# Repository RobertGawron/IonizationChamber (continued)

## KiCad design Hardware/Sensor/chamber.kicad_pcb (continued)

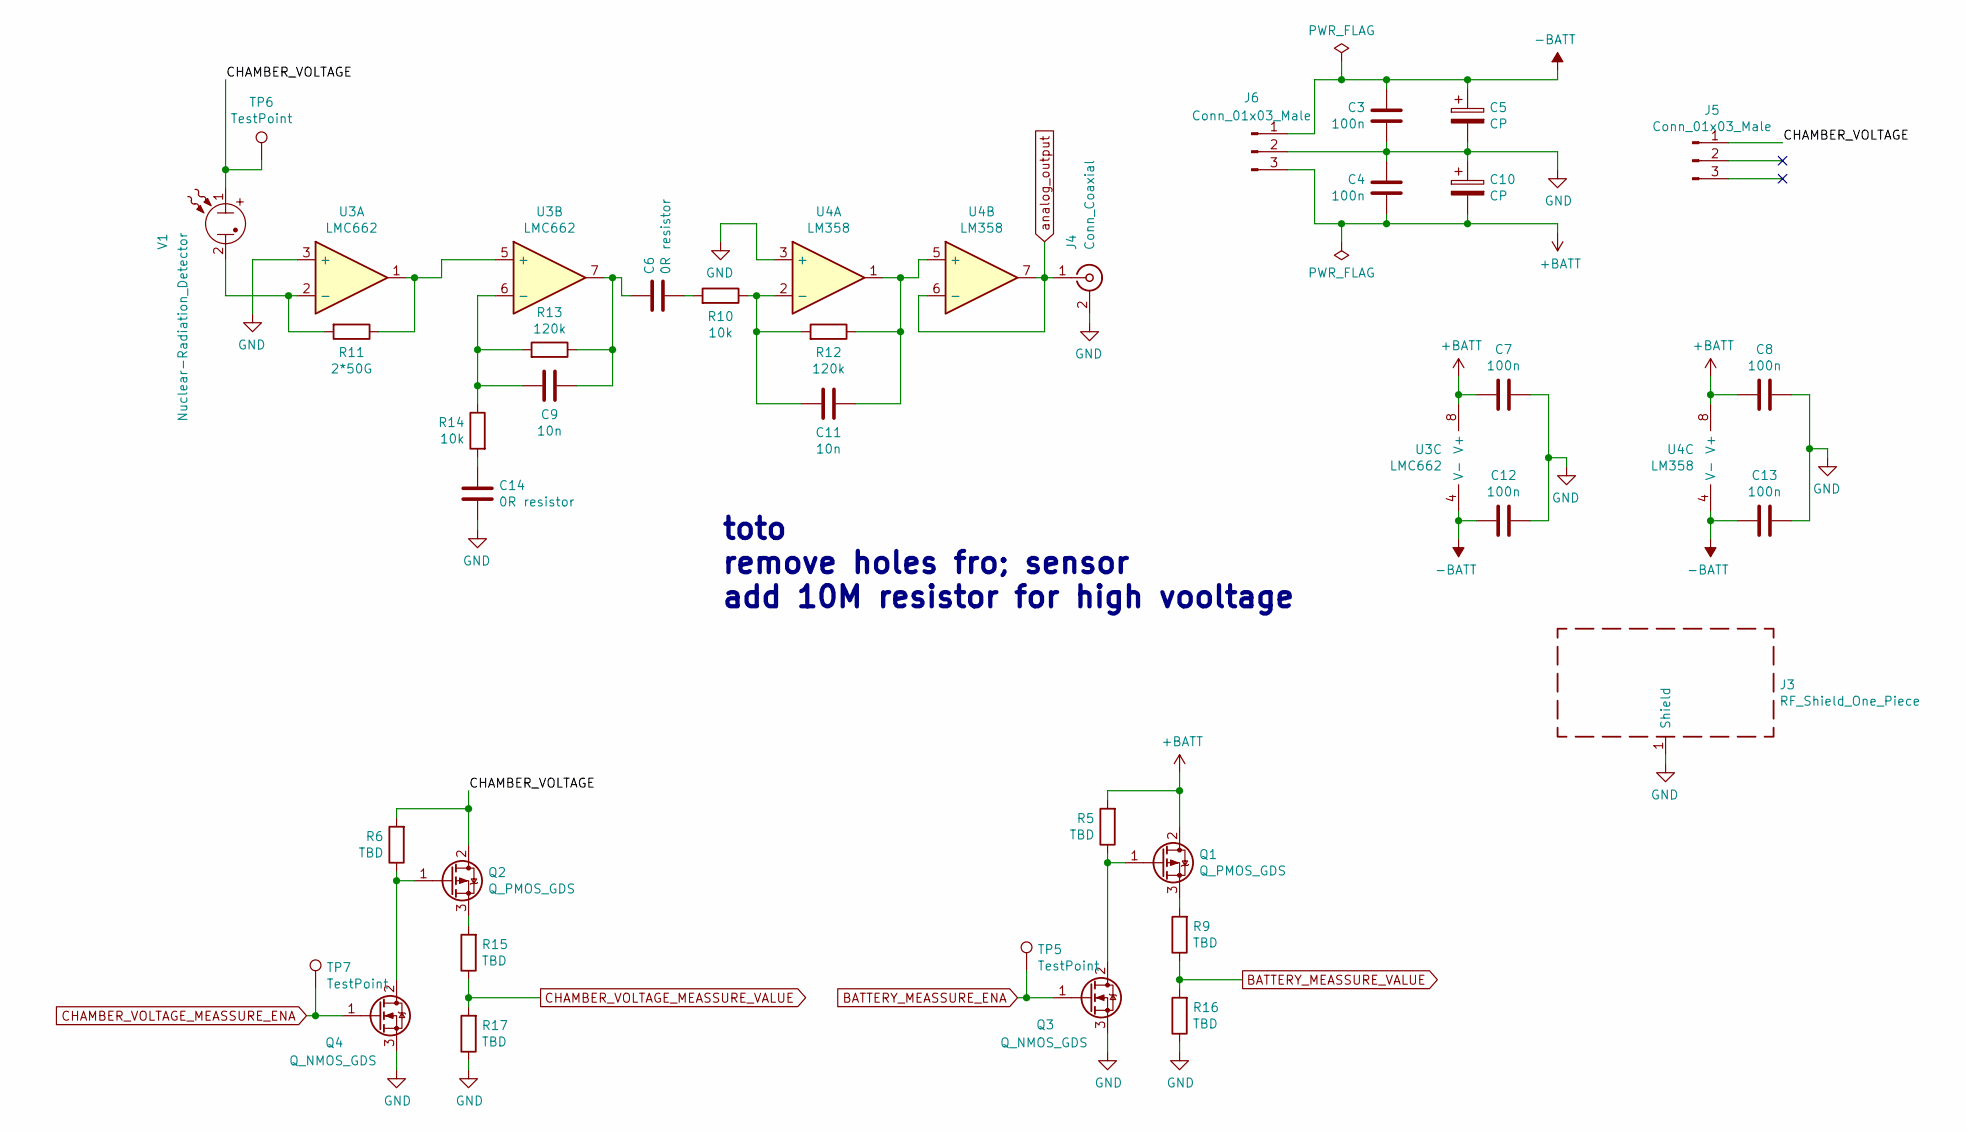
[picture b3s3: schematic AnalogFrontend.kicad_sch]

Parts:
C3, C4, C7, C8, C12, C13: 100n; C_0805_2012Metric; LCSC C282732
C5, C10: CP; CP_Elec_6.3x5.8
C6, C14: 0R resistor; C_0805_2012Metric
C9, C11: 10n; C_0805_2012Metric; LCSC C1710
J3: RF_Shield_One_Piece; RFShield
J4: Conn_Coaxial; SMA_Molex_73251-2200_Horizontal
J5, J6: Conn_01x03_Male; PinSocket_1x03_P2.54mm_Vertical
Q1, Q2: Q_PMOS_GDS; SOT-23
Q3, Q4: Q_NMOS_GDS; SOT-23
R5, R6, R9, R15, R16, R17: TBD; R_0805_2012Metric
R10, R14: 10k; R_0805_2012Metric; LCSC C25744
R11: 2*50G; R_0805_2012Metric
R12, R13: 120k; R_0805_2012Metric; LCSC C17436
TP5, TP7: TestPoint; TestPoint_Pad_D2.0mm
TP6: TestPoint; TestPoint_Loop_D2.60mm_Drill0.9mm_Beaded
U3: LMC662; DIP-8_W7.62mm
U4: LM358; SOIC-8_3.9x4.9mm_P1.27mm; LCSC C7950
V1: Nuclear-Radiation_Detector; IonizationChamberSensor

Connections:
+BATT: C4.1, C7.1, C8.1, C10.2, J6.3, Q1.2 (D), R5.2, U3.8 (V+), U4.8 (V+)
-BATT: C3.2, C5.1, C12.1, C13.1, J6.1, U3.4 (V-), U4.4 (V-)
/AnalogFrontend/CHAMBER_VOLTAGE: J5.1, Q2.2 (D), R6.2, TP6.1, V1.1
BATTERY_MEASSURE_ENA: Q3.1 (G), TP5.1; also elsewhere on the board
BATTERY_MEASSURE_VALUE: R9.1, R15.1, R16.2, R17.2; also elsewhere on the board
CHAMBER_VOLTAGE_MEASSURE_ENA: Q4.1 (G), TP7.1; also elsewhere on the board
GND: C3.1, C4.2, C5.2, C7.2, C8.2, C10.1, C12.2, C13.2, C14.2, J3.1 (Shield), J4.2 (Ext), J6.2, Q3.3 (S), Q4.3 (S), R16.1, R17.1, U3.3 (+), U4.3 (+); also elsewhere on the board
unnamed: C6.1, C9.2, R13.1, U3.7
unnamed: C6.2, R10.2
unnamed: C9.1, R13.2, R14.1, U3.6 (-)
unnamed: C11.1, R10.1, R12.2, U4.2 (-)
unnamed: C11.2, R12.1, U4.1, U4.5 (+)
unnamed: C14.1, R14.2
unnamed: Q1.1 (G), Q3.2 (D), R5.1
unnamed: Q1.3 (S), R9.2
unnamed: Q2.1 (G), Q4.2 (D), R6.1
unnamed: Q2.3 (S), R15.2
unnamed: R11.1, U3.1, U3.5 (+)
unnamed: R11.2, U3.2 (-), V1.2
analog_output: J4.1 (In), U4.6 (-), U4.7; also elsewhere on the board

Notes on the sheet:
toto remove holes fro; sensor add 10M resistor for high vooltage

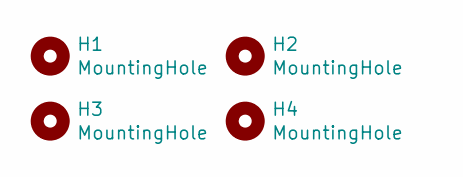
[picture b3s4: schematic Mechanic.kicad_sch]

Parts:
H1, H2, H3, H4: MountingHole; MountingHole_3.5mm

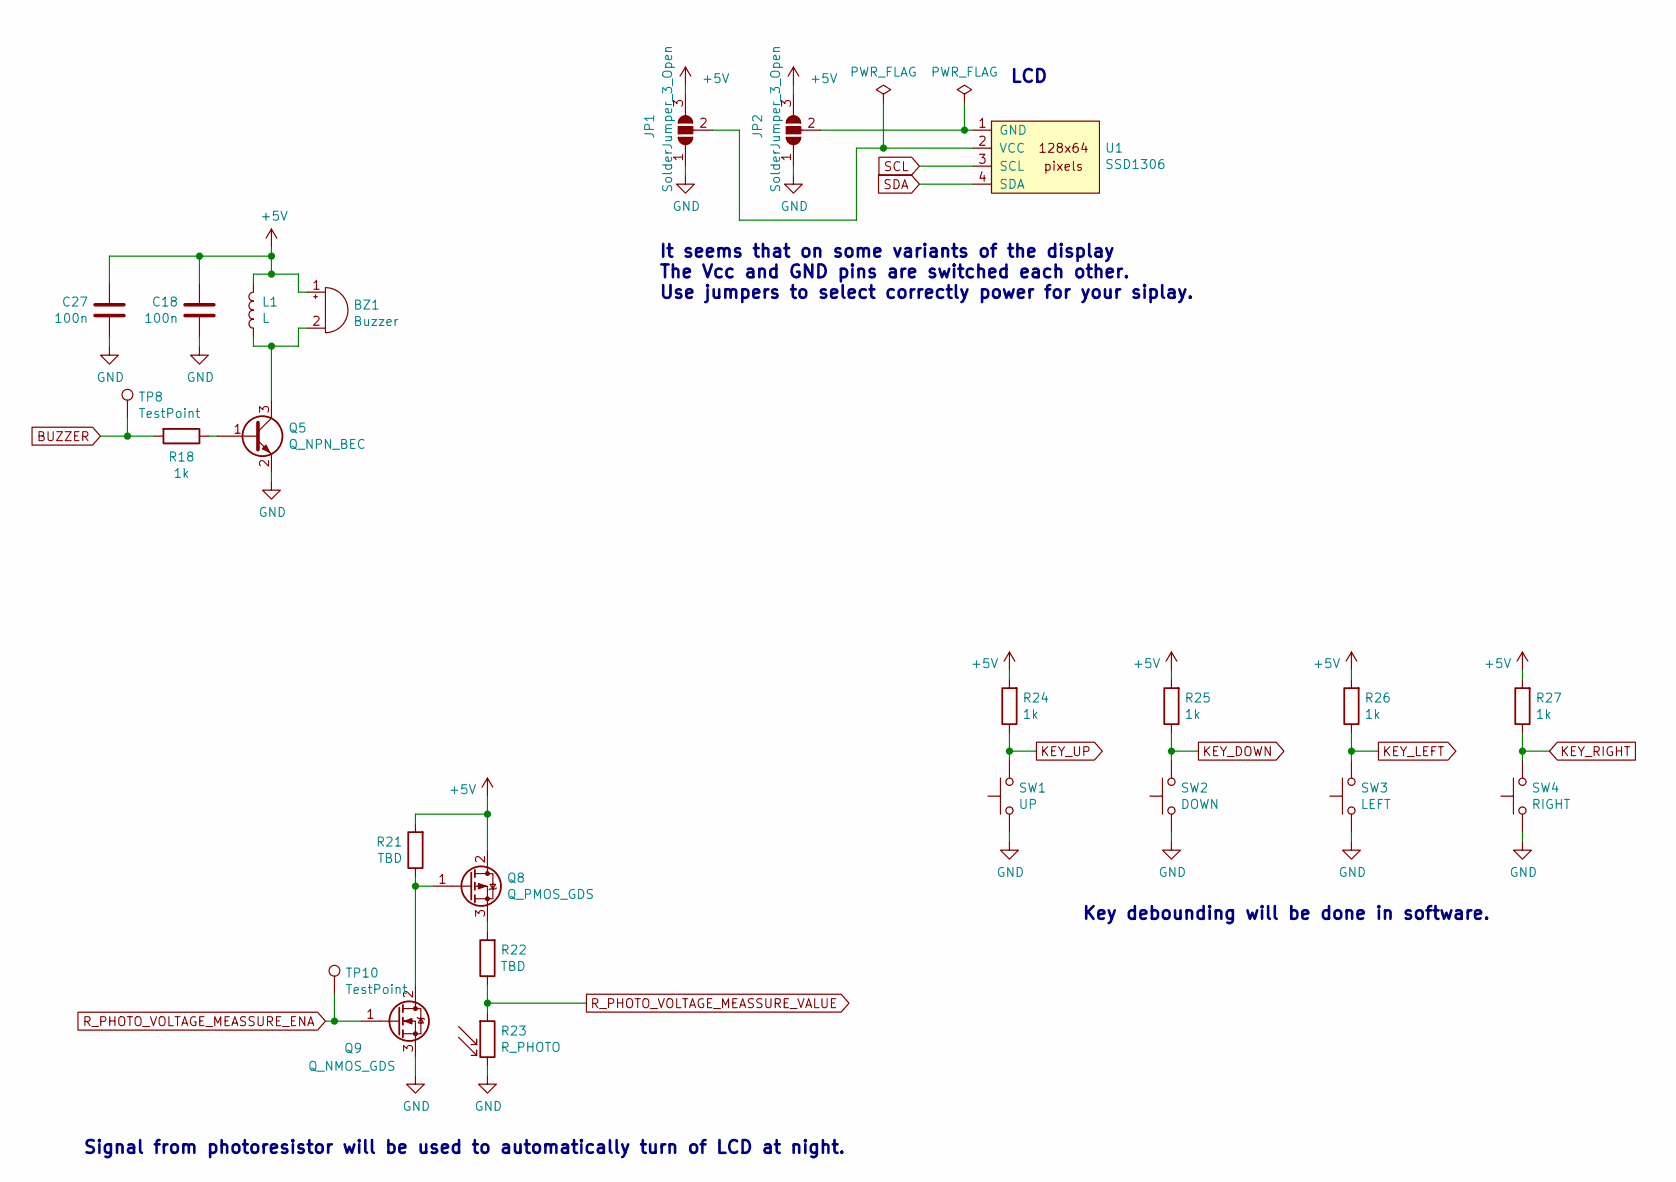
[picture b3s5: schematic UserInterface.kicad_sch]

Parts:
BZ1: Buzzer; LPT1440S-HS-05-4.0-12-R
C18, C27: 100n; C_0805_2012Metric; LCSC C282732
JP1, JP2: SolderJumper_3_Open; SolderJumper-3_P1.3mm_Open_Pad1.0x1.5mm_NumberLabels
L1: L; L_Axial_L5.3mm_D2.2mm_P2.54mm_Vertical_Vishay_IM-1
Q5: Q_NPN_BEC; SOT-23
Q8: Q_PMOS_GDS; SOT-23
Q9: Q_NMOS_GDS; SOT-23
R18, R24, R25, R26, R27: 1k; R_0805_2012Metric; LCSC C17513
R21, R22: TBD; R_0805_2012Metric
R23: R_PHOTO; R_LDR_7x6mm_P5.1mm_Vertical
SW1: UP; SW_SPST_PTS645
SW2: DOWN; SW_SPST_PTS645
SW3: LEFT; SW_SPST_PTS645
SW4: RIGHT; SW_SPST_PTS645
TP8, TP10: TestPoint; TestPoint_Pad_D2.0mm
U1: SSD1306

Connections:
+5V: BZ1.1 (-), C18.1, C27.1, JP1.3 (B), JP2.3 (B), L1.1, Q8.2 (D), R21.2, R24.2, R25.2, R26.2, R27.2; also elsewhere on the board
BATTERY_MEASSURE_VALUE: R22.1, R23.1; also elsewhere on the board
BUZZER: R18.2, TP8.1; also elsewhere on the board
GND: C18.2, C27.2, JP1.1 (A), JP2.1 (A), Q5.2 (E), Q9.3 (S), R23.2, SW1.2, SW2.2, SW3.2, SW4.2; also elsewhere on the board
KEY_DOWN: R25.1, SW2.1; also elsewhere on the board
KEY_LEFT: R26.1, SW3.1; also elsewhere on the board
KEY_RIGHT: R27.1, SW4.1; also elsewhere on the board
KEY_UP: R24.1, SW1.1; also elsewhere on the board
unnamed: BZ1.2 (+), L1.2, Q5.3 (C)
unnamed: JP1.2 (C), U1.2 (VCC)
unnamed: JP2.2 (C), U1.1 (GND)
unnamed: Q5.1 (B), R18.1
unnamed: Q8.1 (G), Q9.2 (D), R21.1
unnamed: Q8.3 (S), R22.2
R_PHOTO_VOLTAGE_MEASSURE_ENA: Q9.1 (G), TP10.1; also elsewhere on the board
SCL: U1.3 (SCL); also elsewhere on the board
SDA: U1.4 (SDA); also elsewhere on the board

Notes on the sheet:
Signal from photoresistor will be used to automatically turn of LCD at night.
It seems that on some variants of the display The Vcc and GND pins are switched each other. Use jumpers to select correctly power for your siplay.
LCD
Key debounding will be done in software.

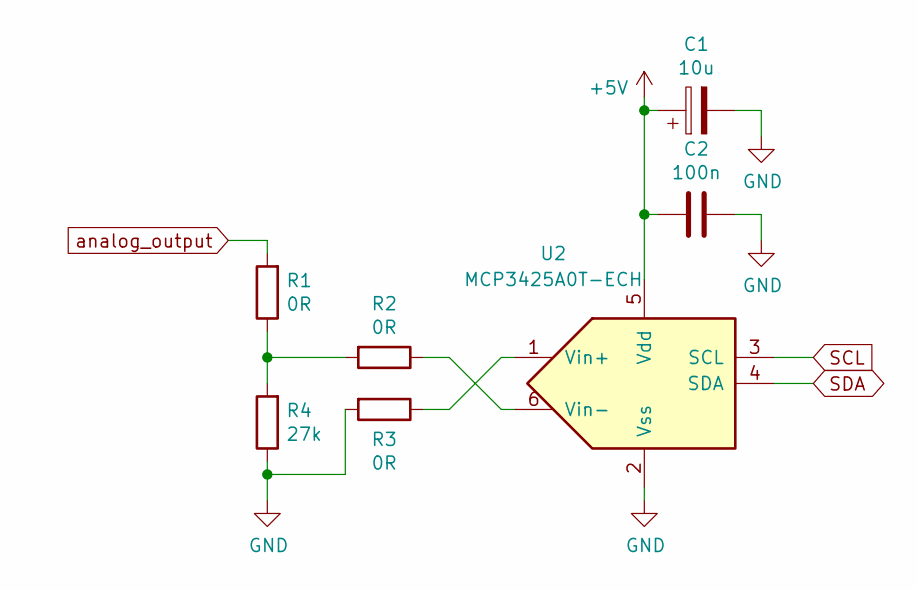
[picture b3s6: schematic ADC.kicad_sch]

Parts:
C1: 10u; CP_EIA-3528-21_Kemet-B
C2: 100n; C_0805_2012Metric; LCSC C282732
R1, R2, R3: 0R; R_0805_2012Metric; LCSC C17477
R4: 27k; R_0805_2012Metric; LCSC C17593
U2: MCP3425A0T-ECH; SOT-23-6_Handsoldering

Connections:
+5V: C1.1, C2.2, U2.5 (Vdd); also elsewhere on the board
GND: C1.2, C2.1, R3.2, R4.1, U2.2 (Vss); also elsewhere on the board
unnamed: R1.1, R2.2, R4.2
unnamed: R2.1, U2.6 (Vin-)
unnamed: R3.1, U2.1 (Vin+)
SCL: U2.3 (SCL); also elsewhere on the board
SDA: U2.4 (SDA); also elsewhere on the board
analog_output: R1.2; also elsewhere on the board

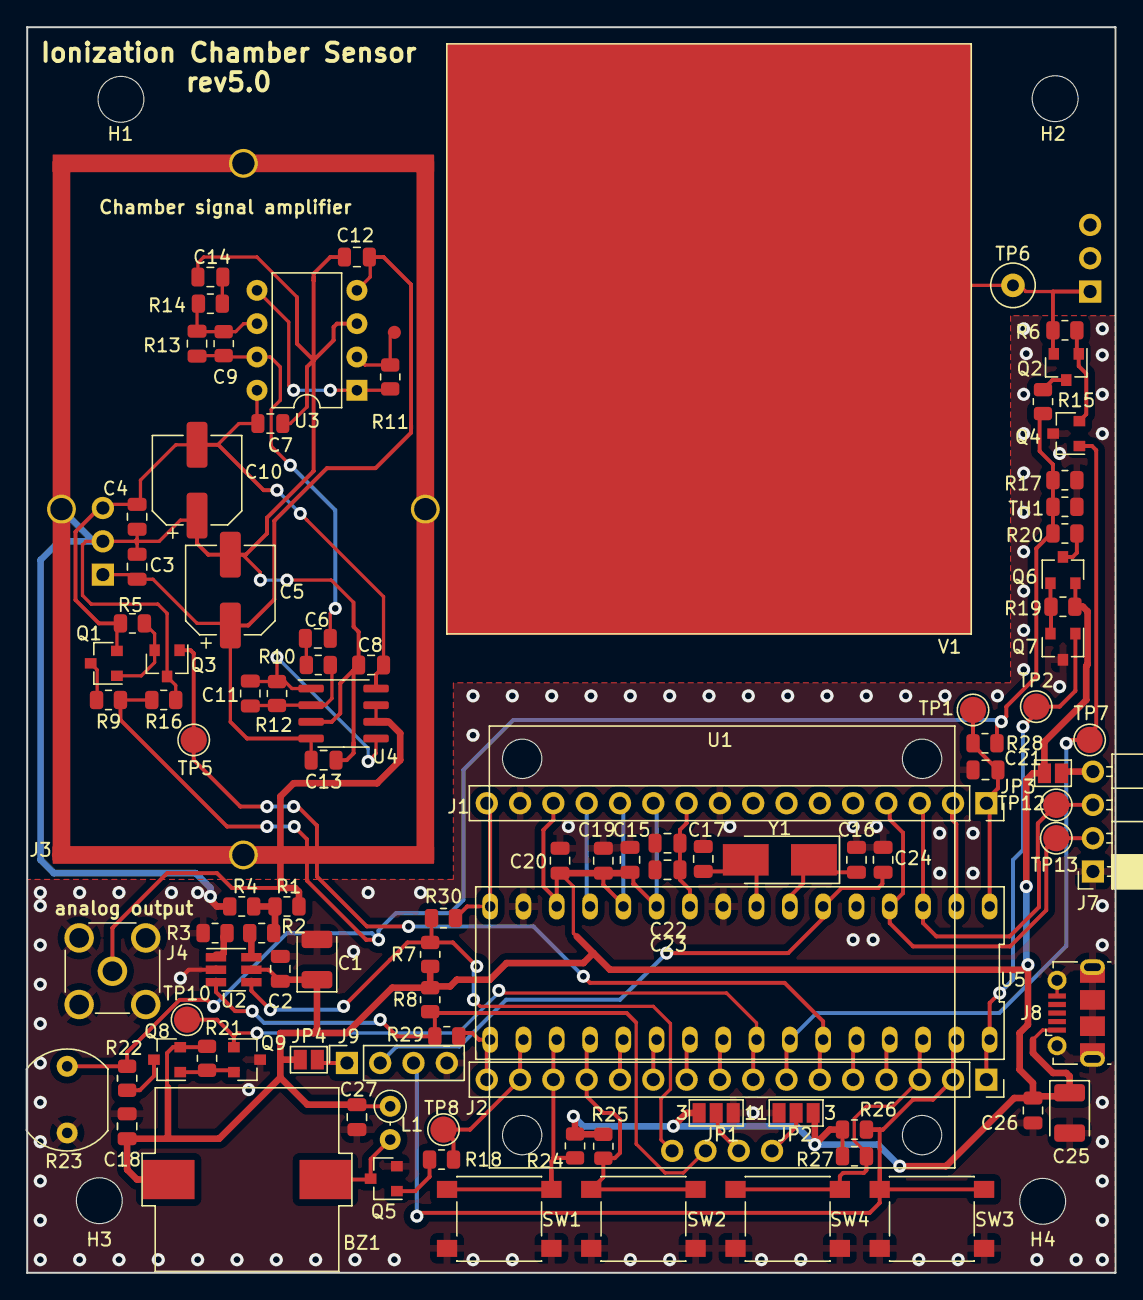
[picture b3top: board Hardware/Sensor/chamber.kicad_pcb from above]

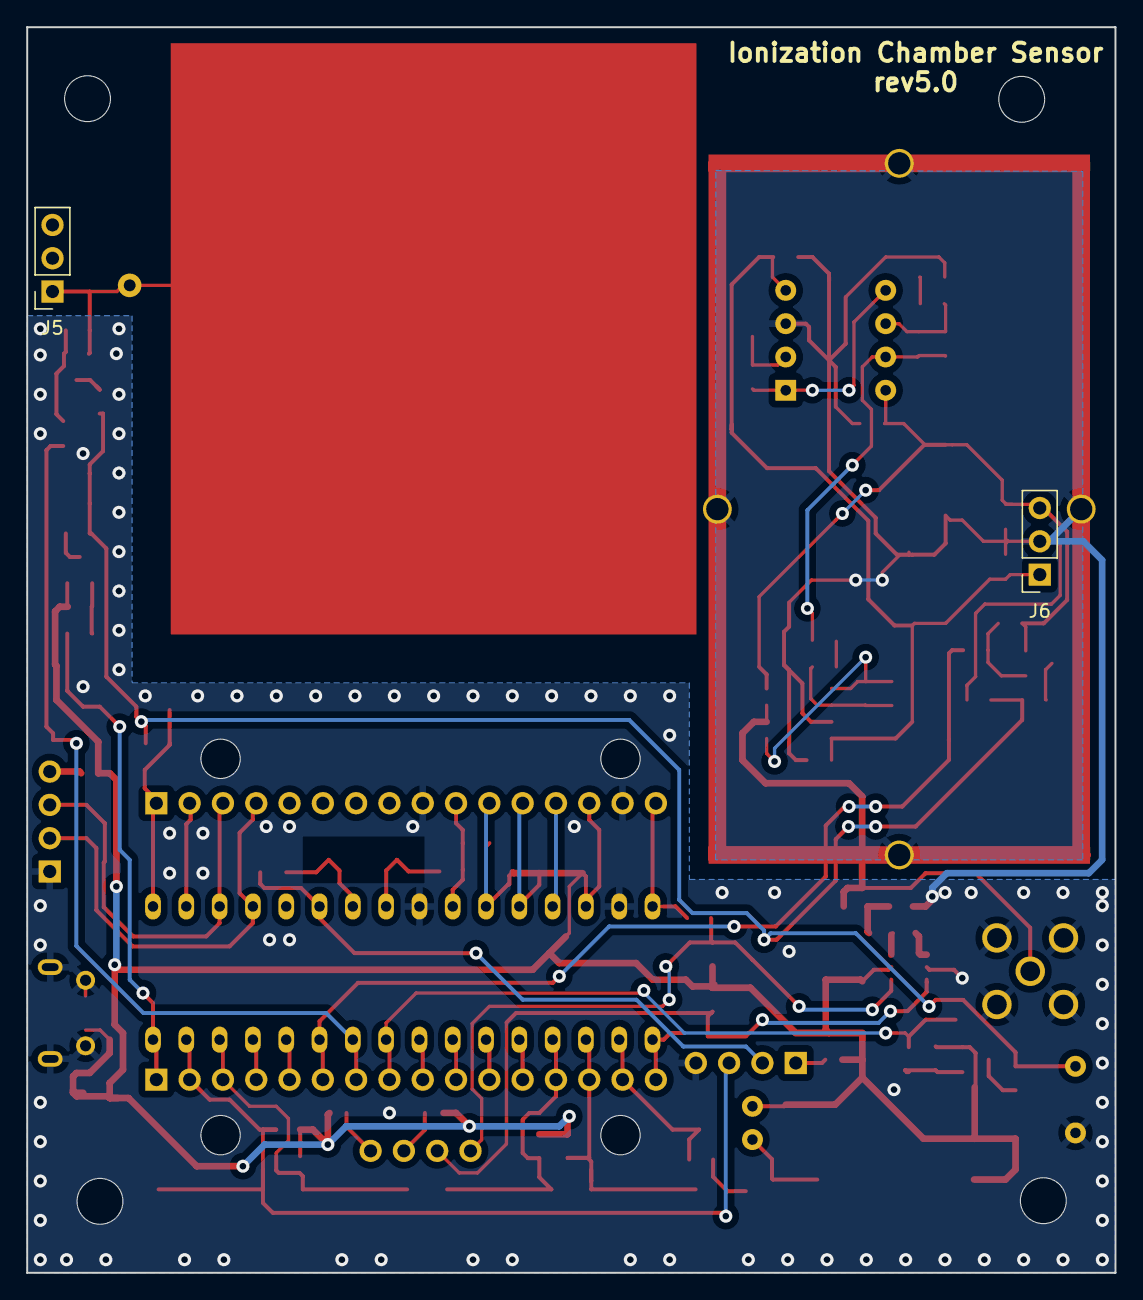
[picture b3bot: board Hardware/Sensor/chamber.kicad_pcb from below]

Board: 2 copper layers, 83.0 x 95.0 mm, 106 parts (2 on the bottom side), 60 nets.

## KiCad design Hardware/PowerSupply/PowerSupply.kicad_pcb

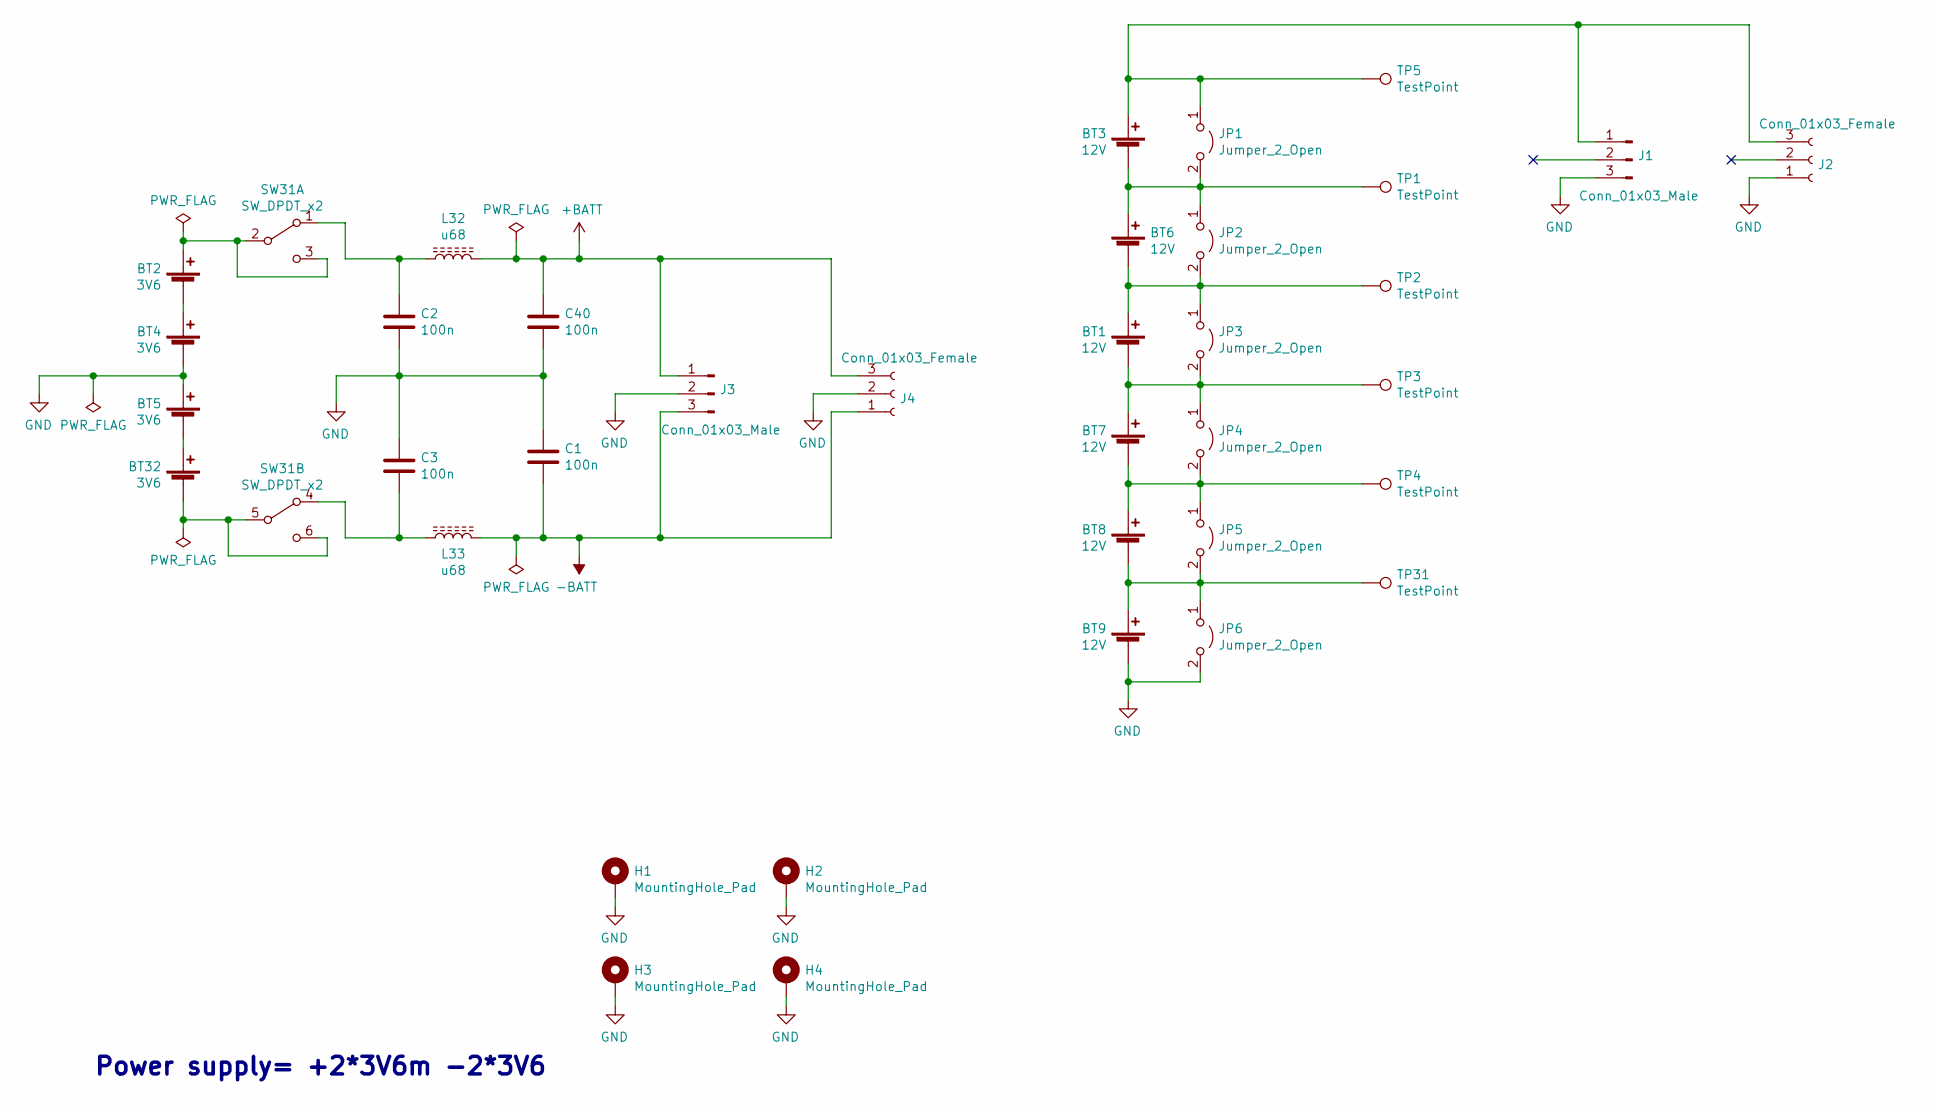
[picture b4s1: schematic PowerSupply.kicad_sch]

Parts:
BT1, BT3, BT6, BT7, BT8, BT9: 12V; 27ABatteryHolder
BT2, BT4, BT5, BT32: 3V6; MR18650BatteryHolder
C1, C2, C3, C40: 100n; C_0805_2012Metric
H1, H2, H3, H4: MountingHole_Pad; MountingHole_3.5mm_Pad
J1, J3: Conn_01x03_Male; PinHeader_1x03_P2.54mm_Vertical
J2, J4: Conn_01x03_Female; PinSocket_1x03_P2.54mm_Vertical
JP1, JP2, JP3, JP4, JP5, JP6: Jumper_2_Open; SolderJumper-2_P1.3mm_Open_Pad1.0x1.5mm
L32, L33: u68; L_1812_4532Metric_Pad1.30x3.40mm_HandSolder
SW31: SW_DPDT_x2; SW_E-Switch_EG1271_DPDT
TP1, TP2, TP3, TP4, TP5, TP31: TestPoint; TestPoint_Pad_D3.0mm

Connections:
+BATT: C40.2, J3.1, J4.3, L32.1
-BATT: C1.1, J3.3, J4.1, L33.1
GND: BT4.2 (-), BT5.1 (+), BT9.2 (-), C1.2, C2.1, C3.2, C40.1, H1.1, H2.1, H3.1, H4.1, J1.3, J2.1, J3.2, J4.2, JP6.2 (B)
unnamed: BT1.1 (+), BT6.2 (-), JP2.2 (B), JP3.1 (A), TP2.1
unnamed: BT1.2 (-), BT7.1 (+), JP3.2 (B), JP4.1 (A), TP3.1
unnamed: BT2.1 (+), SW31.2 (B), SW31.3 (C)
unnamed: BT2.2 (-), BT4.1 (+)
unnamed: BT3.1 (+), J1.1, J2.3, JP1.1 (A), TP5.1
unnamed: BT3.2 (-), BT6.1 (+), JP1.2 (B), JP2.1 (A), TP1.1
unnamed: BT7.2 (-), BT8.1 (+), JP4.2 (B), JP5.1 (A), TP4.1
unnamed: BT8.2 (-), BT9.1 (+), JP5.2 (B), JP6.1 (A), TP31.1
unnamed: BT5.2 (-), BT32.1 (+)
unnamed: BT32.2 (-), SW31.5 (B), SW31.6 (C)
unnamed: C2.2, L32.2, SW31.1 (A)
unnamed: C3.1, L33.2, SW31.4 (A)

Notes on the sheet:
Power supply= +2*3V6m -2*3V6

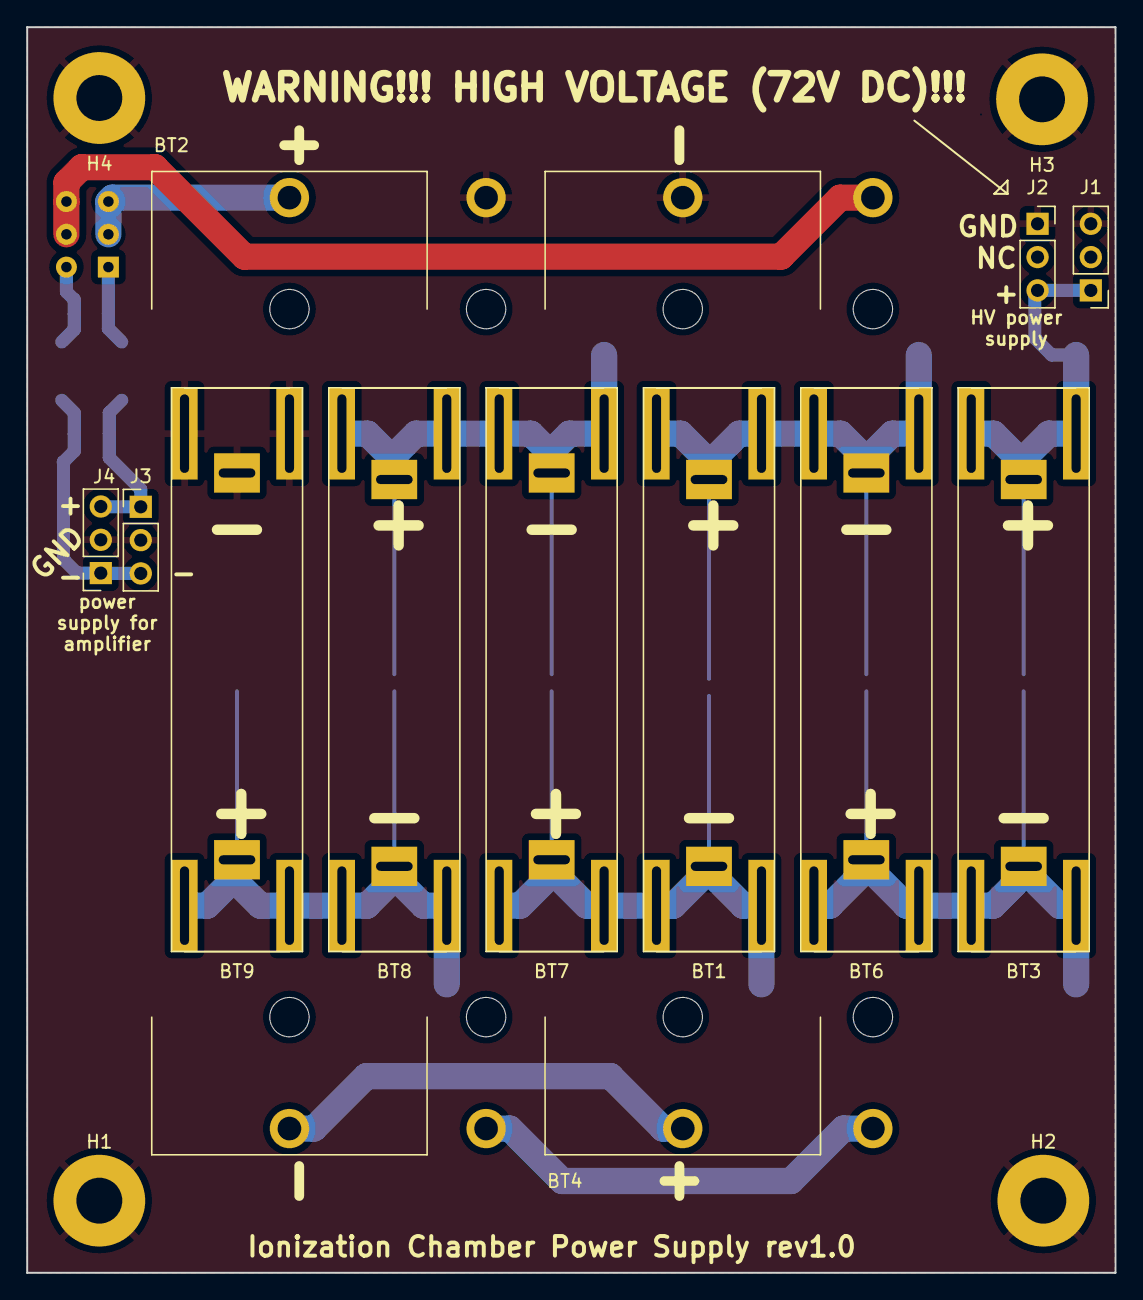
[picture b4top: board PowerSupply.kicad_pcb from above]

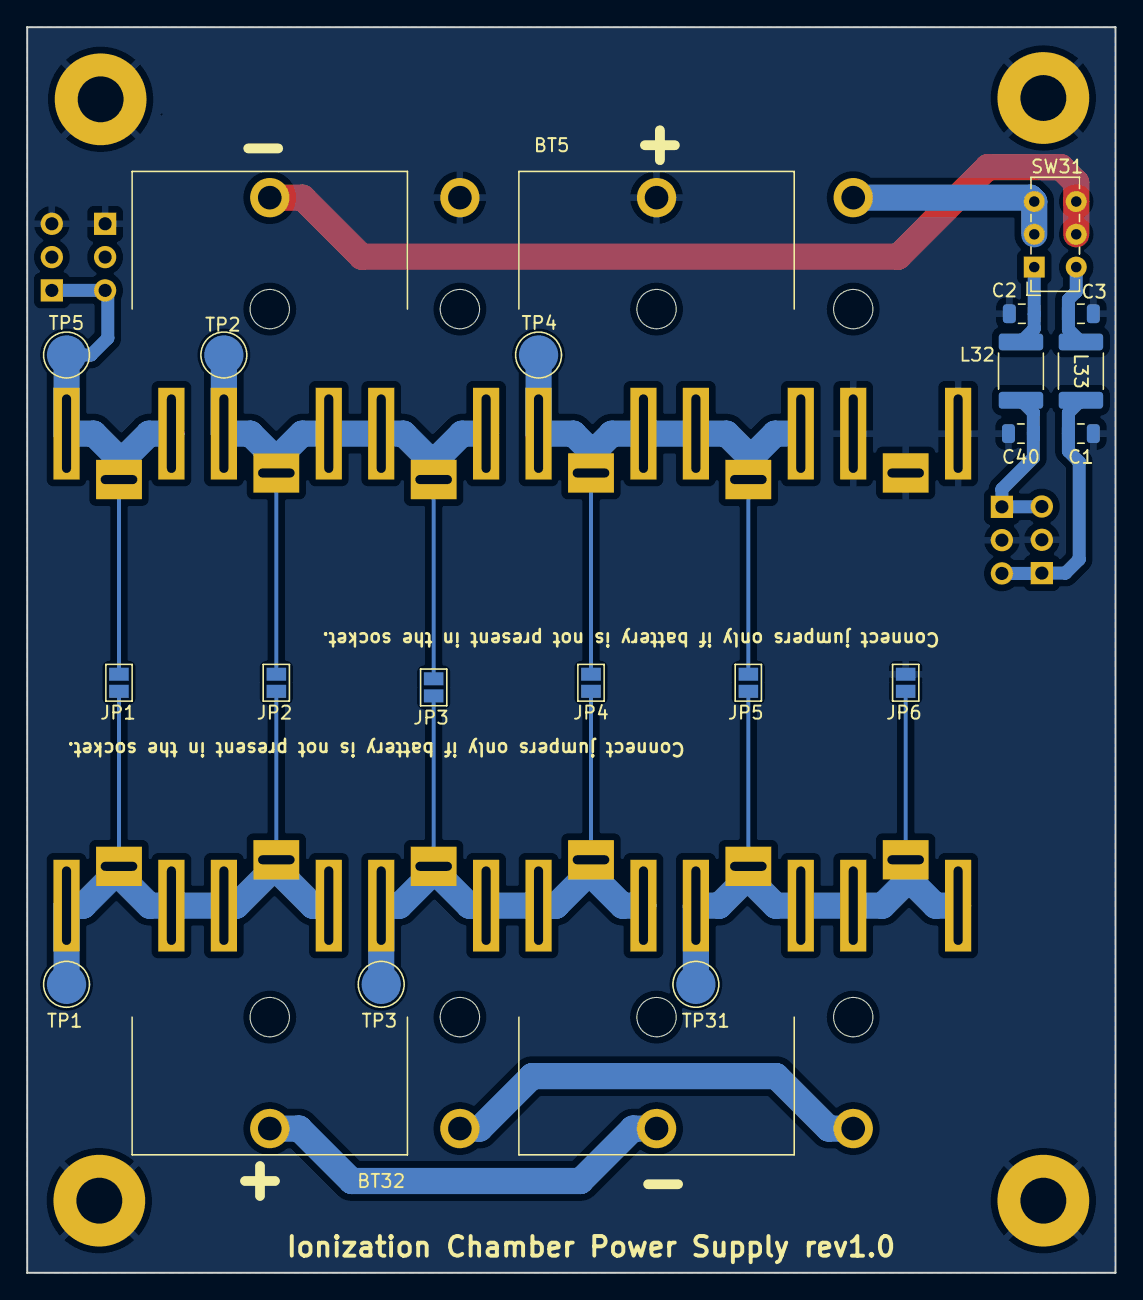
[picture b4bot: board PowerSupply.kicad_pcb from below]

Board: 2 copper layers, 83.0 x 95.0 mm, 37 parts (21 on the bottom side), 15 nets.
